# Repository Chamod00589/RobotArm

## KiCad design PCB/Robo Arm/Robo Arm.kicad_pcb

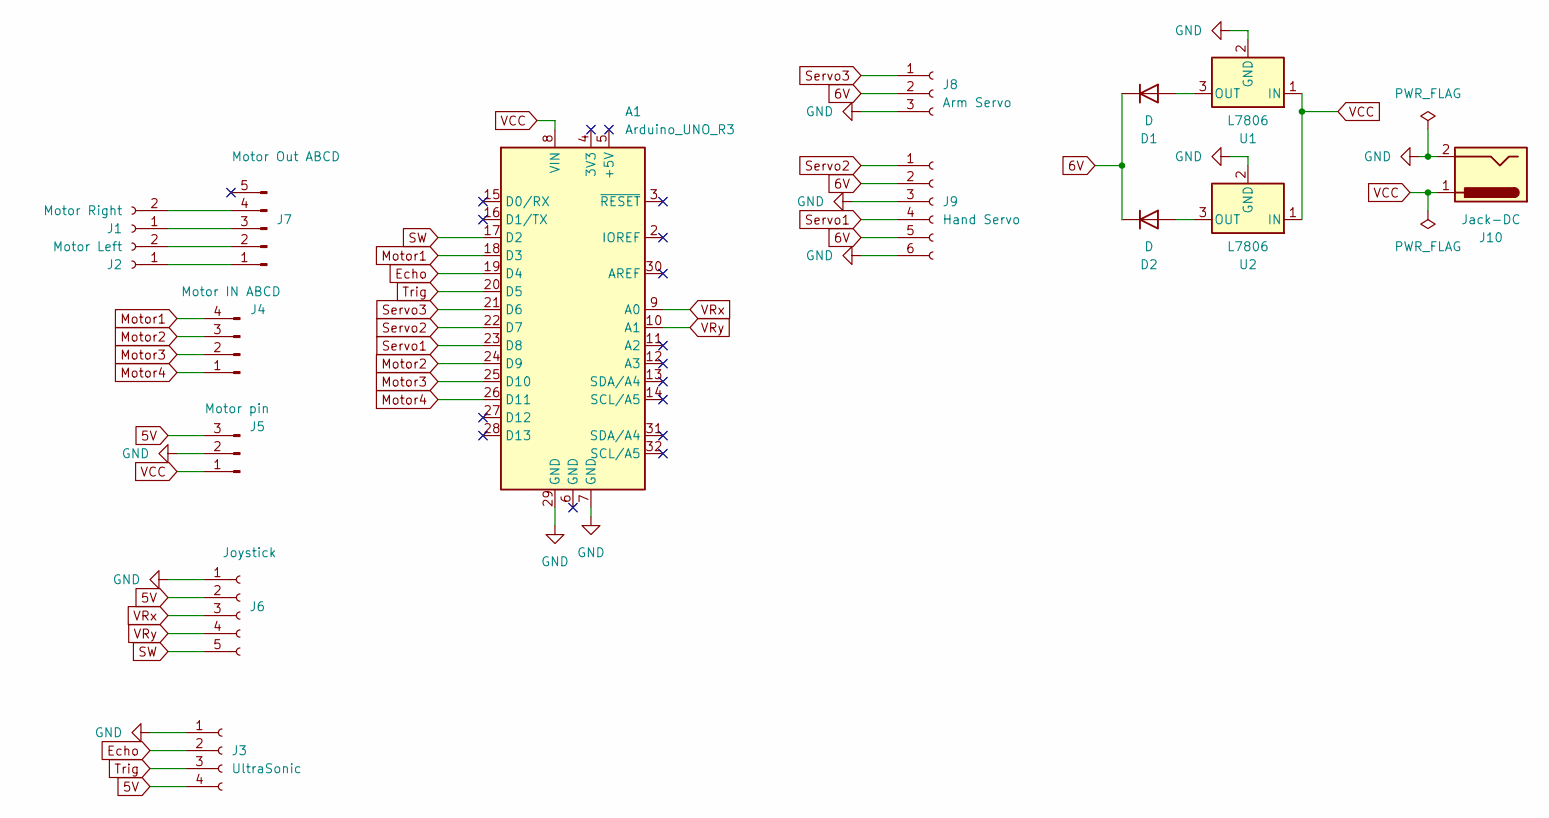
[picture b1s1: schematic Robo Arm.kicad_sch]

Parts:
A1: Arduino_UNO_R3
D1, D2: D; D_DO-15_P5.08mm_Vertical_KathodeUp
J1: Motor Right; PinHeader_1x02_P2.54mm_Vertical
J2: Motor Left; PinHeader_1x02_P2.54mm_Vertical
J3: UltraSonic; PinSocket_1x04_P2.54mm_Vertical
J4: Motor IN ABCD; PinHeader_1x04_P2.54mm_Vertical
J5: Motor pin; PinHeader_1x03_P2.54mm_Vertical
J6: Joystick; PinHeader_1x05_P2.54mm_Vertical
J7: Motor Out ABCD; JST_XH_B5B-XH-A_1x05_P2.50mm_Vertical
J8: Arm Servo; JST_XH_B3B-XH-A_1x03_P2.50mm_Vertical
J9: Hand Servo; JST_XH_B6B-XH-A_1x06_P2.50mm_Vertical
J10: Jack-DC; BarrelJack_CUI_PJ-063AH_Horizontal
U1, U2: L7806; TO-220-3_Vertical

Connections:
5V: J3.4, J5.3, J6.2
6V: D1.1 (K), D2.1 (K), J8.2, J9.2, J9.5
Echo: A1.19 (D4), J3.2
GND: A1.7 (GND), A1.29 (GND), J3.1, J5.2, J6.1, J8.3, J9.3, J9.6, J10.2, U1.2 (GND), U2.2 (GND)
Motor1: A1.18 (D3), J4.4
Motor2: A1.24 (D9), J4.3
Motor3: A1.25 (D10), J4.2
Motor4: A1.26 (D11), J4.1
unnamed: D1.2 (A), U1.3 (OUT)
unnamed: D2.2 (A), U2.3 (OUT)
unnamed: J1.1, J7.3
unnamed: J1.2, J7.4
unnamed: J2.1, J7.1
unnamed: J2.2, J7.2
SW: A1.17 (D2), J6.5
Servo1: A1.23 (D8), J9.4
Servo2: A1.22 (D7), J9.1
Servo3: A1.21 (D6), J8.1
Trig: A1.20 (D5), J3.3
VCC: A1.8 (VIN), J5.1, J10.1, U1.1 (IN), U2.1 (IN)
VRx: A1.9 (A0), J6.3
VRy: A1.10 (A1), J6.4

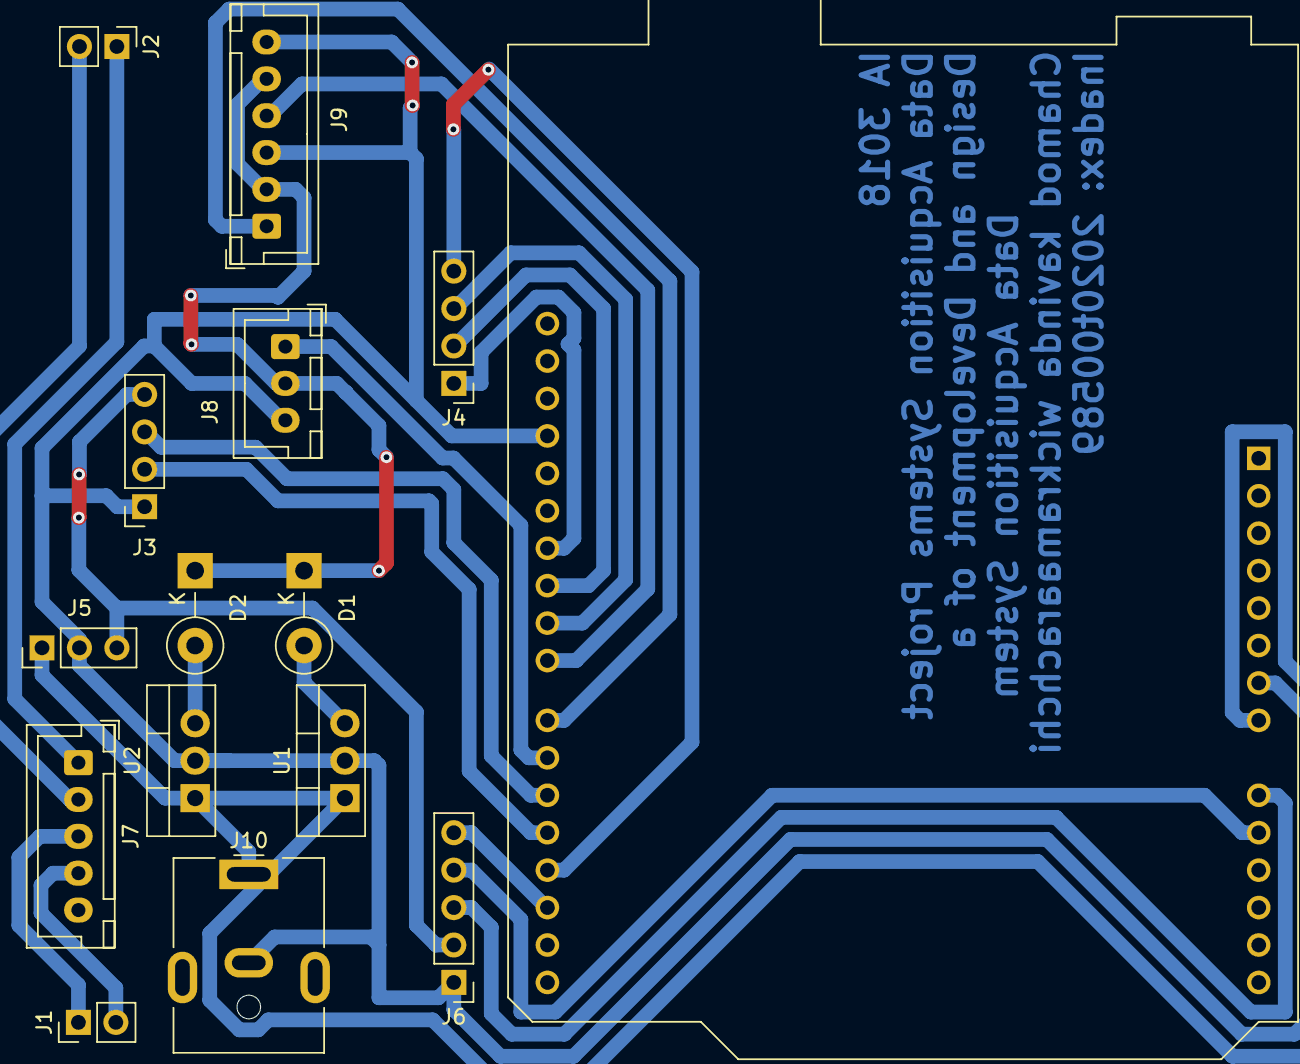
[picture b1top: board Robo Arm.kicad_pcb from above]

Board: 2 copper layers, 15 parts (0 on the bottom side), 22 nets.

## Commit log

2023-12-23 Create c# app
2023-12-24 Test Serial Connection OK
2023-12-24 Complete ui functions
2024-01-01 complete
2024-01-02 compelete
